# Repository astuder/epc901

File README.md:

# Introduction
The [ESPROS epc901](https://www.espros.com/photonics/epc901/) is a CCD line sensor with a resolution of 1024 monochrome pixels.

Compared to other image sensors the epc901 is very easy to drive, requiring only one voltage, I2C, a few digital I/Os and an ADC. It is also available for [$33 in single units from Digi-key](https://www.digikey.com/en/products/detail/espros-photonics-ag/EPC901-CSP32-033/10516882). On the downside, the sensor
comes in a BGA package, the evaluation kit is [very expensive at $1400](https://www.digikey.com/en/products/detail/espros-photonics-ag/EPC901-EVALUATION-KIT-V1/10516848),
and we haven't seen this sensor from any other distributors than Digi-key.

This repository contains design files to build hardware and software to interact with the sensor. 

For Windows users, there's now also a [version of g3gg0.de SpectrumPlotter](https://github.com/astuder/epc901SpectrumPlotter) adapted to work with my epc901 firmware.

@fmilburn3 posted a write-up of this project and a few spectroscopy experiments on [element14](https://www.element14.com/community/community/project14/sensors/blog/2020/11/11/spectrography-using-the-epc901-high-speed-line-image-sensor).

## Table of contents

[Hardware](#hardware)
* [Breakout board](#breakout-board)
  * [Connector pinout](#connector-pinout)
  * [Jumpers](#jumpers)
  * [Config resistor array](#config-resistor-array)
  * [Physical dimensions](#physical-dimensions)
  * [Lens holder & lens](#lens-holder--lens)
* [Adapter board](#adapter-board)
  * [Pin mapping](#pin-mapping)
  * [Jumpers](#jumpers)
* [Shared](#shared)
* [Spectroscope tube](#spectroscope-tube)

[Software](#software)
* [Firmware](#firmware)
  * [Shell](#shell)
  * [Capture logic](#capture-logic)
  * [Trigger logic](#trigger-logic)
  * [Transfer format](#transfer-format)
* [Python](#python)
  * [epc901camera.py](#epc901camerapy)
  * [example scripts](#example-scripts)
 
[License](#license)

# Hardware

All hardware in this project is designed with KiCad version 5.1.6.

The hardware consists of a breakout board for the image sensor, and an adapter board for vertically mounting the breakout board on an ST Nulceo-144 development board.

## Breakout board

The folder [```./hardware/breakout```](./hardware/breakout) contains the KiCad project for the epc901 breakout board.

The image sensor comes in a 2x16, 0.5 mm pitch BGA package and looks very fragile. With careful handling and placement, we successfully assembled a few boards
using a stainless steel solder stencil and an unmodified toaster oven for reflow. Reflow on a hotplate probably works as well.

In addition to the image sensor and related passives, the breakout board also integrates an ADC. Footprint and firmware are compatible with [Texas Instruments ADCS7476](https://www.ti.com/product/ADCS7476) and [Analog Devices AD7476](https://www.analog.com/en/products/ad7476.html) which are 1 MSPS 12-bit ADCs with SPI-like interface.

The PCB can be ordered from OSH Park using this [link](https://oshpark.com/shared_projects/5eUl3QVW).

### Connector pinout

Pin|Function|Comment
-|-|-
1|GND|digital ground
2|PWR_DOWN|see epc901 datasheet
3|DATA_RDY|see epc901 datasheet
4|CLR_DATA|see epc901 datasheet
5|SHUTTER|see epc901 datasheet
6|CLR_PIX|see epc901 datasheet
7|GNDA|analog ground
8|VIDEO_P|positive video signal for use w/ external ADC, see epc901 datasheet
9|VIDEO_N|negative video signal for use w/ external ADC, see epc901 datasheet
10|GNDA|analog ground
11|GND|digital ground
12|ADC_CLK|SPI clk to on-board ADC
13|ADC_DATA|SPI data from on-board ADC
14|ADC_CS|SPI chip select for on-board ADC
15|GND|digital ground
16|3V3|3.3V power supply
17|GND|digital ground
18|READ|see epc901 datasheet
19|SDA|I2C data
20|SCL|I2C clock

### Jumpers

ID|Function|Comment
-|-|-
JP1|STAR GND|Star ground point between GND and GNDA. Close to connect, leave open if GNDA and GND are connected off-board.
JP2|ADC SELECTION|Selects whether to use the on-board ADC or an external ADC. External ADC will route VIDEO_P to pin 8 in the connector.

### Config resistor array

These resistors control the configuration of the image sensor on power-up. For details, see sections 4, 7.1 and 12 in the epc901 datasheet.

### Physical dimensions

The size of the board is 61 x 36 mm. The mounting holes in the corners are spaced 55 x 30 mm and have a diameter of 2.2 mm, designed for M2 screws.

The mounting holes for the lens holder are located 29 mm from the left board edge and 8 mm from top and bottom board edge. They have a diameter of 2.2 mm, designed for M2 screws.

### Lens holder & lens

The breakout board has space and mounting holes for a lens holder. The spacing between the mounting holes is 20mm. For full coverage, the lens should support 1/2.3" or larger sensors.

For our prototypes, we chose a [M12 metal lens holder w/ 20mm hole spacing](https://www.m12lenses.com/CNC-Machined-M12-Lens-Holder-Metal-p/pt-lh031m.htm) and a [25mm M12 lens for 1/2" sensors](https://www.m12lenses.com/25mm-F2-4-5MP-CCTV-Lens-p/pt-2524mp5y.htm). In the US, a wide selection of lens holders and lenses can be found at [M12 Lenses Inc](https://www.m12lenses.com).

For use in a spectrograph, a lens may not be required. However we recommend protecting the sensor against accidental physical damage with some sort of bracket or baffel.

## Adapter board

The folder [```./hardware/adapter-shield```](./hardware/adapter-shield) contains the KiCad project for an adapter to mount the 
epc901 breakout board on the NUCLEO evaluation board.

The layout of the adapter board follows the Arduino Shield standard. This means you could mount the adapter and sensor breakout board on any compatible MCU board. Though
you will likely have to adapt the firmware to make it work.

The PCB can be ordered from OSH Park using this [link](https://oshpark.com/shared_projects/md99YXCX).

### Pin mapping

|Arduino|Nucleo|L496ZG|Breakout|Comment
|-|-|-|-|-
|+3V3|CN8 7|+3V3||Connected to JP1.
|+5V|CN8 9|+5V||Connected to 3.3V LDO.
|GND|CN8 11|GND|GND|
|GND|CN8 13|GND|GND|
|D0|CN10 16|PD9|PWR_DOWN|
|D1|CN10 14|PD8|DATA_RDY|
|D2|CN10 12|PF15|CLR_DATA|
|D3|CN10 10|PE13|SHUTTER|Controlled by TIM1_CH3.
|D4|CN10 8|PF14|CLR_PIX|
|D9|CN7 18|PD15|READ|
|D10|CN7 16|PD14|ADC_CS|
|D12/MISO|CN7 12|PA6|ADC_DATA|
|D13/SCK|CN7 10|PA5|ADC_CLK|
|GND|CN7 8|GND|GND|
|A0|CN9 1|PA3|VIDEO_P|
|A1|CN9 3|PC0|VIDEO_N|
||CN10 1|AVDD||Connected to JP3, reserved to supply analog power from Nucleo in future revisions.
||CN10 3|AVSS||Connected to JP4, alternative source for analog ground from Nucleo.
||CN10 5|GND|GND|
||CN10 7|PB1|VIDEO_P|Alternative analog pins for use with AVDD and AVSS connection in future revisions.
||CN10 9|PC2|VIDEO_N|Alternative analog pins for use with AVDD and AVSS connection in future revisions.

### Jumpers

ID|Function|Comment
-|-|-
JP1|3.3V VCC|Select between LDO on adapter or Nucleo (HOST) as source for 3.3V power supply to breakout board.
JP2|* GND|Star ground point between GND and GNDA. Close to connect, leave open if GNDA and GND are connected on breakout board.
JP3|AVDD|Reserved for future use to supply power to VDD_OA of the EPC901 from the Nucleo.
JP4|AVSS|Star ground point between analog ground of the breakout board and analog ground of the Nucleo. May be useful when using the ADCs of the STM32.

## Shared

The folder [```./hardware/shared```](./hardware/shared) contains custom KiCad symbols, footprints and 3d models that can be reused across KiCad projects in this repository.

## Spectroscope tube

For spectroscopy experiments we created a tube to mount an optical slit and difraction grating. The 3D model is available in the folder [```./hardware/spectroscope-tube```](./hardware/spectroscope-tube).

# Software

## Firmware

The folder [```./software/breakout```](./software/breakout) contains the firmware to control the epc901 breakout board with an
STM32L4 using the [NUCLEO-L496ZG evaluation board](https://www.digikey.com/en/products/detail/stmicroelectronics/NUCLEO-L496ZG/6697037). This specific MCU and
evaluation board were chosen because we had one laying around.

The firmware is developed and built with the latest version of STM32CubeIDE (version 1.4.2 as of October 2020). To import the project into STM32CubeIDE, clone this
repository, open STM32CubeIDE and import the project with ```File > Open Project From File System..```, and select the folder ```./software/breakout```. Follow the standard
procedure for building the firmware and programming the NUCLEO evaluation board.

### Shell

The firmware exposes a command shell over serial. The parameters of the serial connection are 115200 8N1.

Preceding a command with @ will suppress local echo and command prompt, which is useful when developing an application that interacts with the shell.

Most commands that configure an aspect of the firmware return the current setting if no value is provided. For example ```exposure``` will return the currently configured exposure time.

|Command|Description|
|-|-|
|help|Display list of available commands.|
|help COMMAND|Display help text for command.|
|echo ON/OFF|Turn local echo on or off.|
|regread REGISTER|Read register of image sensor over I2C.|
|regwrite REGISTER VALUE|Write to value to register of image sensor over I2C.|
|reset mcu|Reset the STM32 microcontroller.|
|reset camera|Reset the camera settings, for example exposure or burst, to their defaults.|
|reset sensor|Software reset of the image sensor through I2C.|
|exposure TIME_US|Set exposure time in microseconds.|
|exposure max|Get maximum exposure time supported.|
|capture|Start capture using the configured settings.|
|capture abort|If there's a capture in progress, abort current capture.|
|transfer|read next image from the frame buffer.|
|transfer all|read all images available in the frame buffer.|
|transfer last|read last image from frame buffer, all other images will be discarded.|
|burst ON/OFF|turn burst mode on or off.|
|burst fast|Turn on burst mode with fast capture, where image capture and data read out overlap. This can result in noisier data than regular burst mode.|
|burst frames COUNT|Set number of frames to capture in a burst.|
|burst interval TIME_MS|Set interval in milliseconds at which frames are captured. 0 will capture frames at the maximum speed possible.|
|trigger ON/OFF|Enable or disable trigger.|
|trigger source EXTERNAL/LEVEL/ZONE|Select source of trigger signal.|
|trigger direction RISING/FALLING|Set which direction of a signal will trigger. for ```level``` and ```zone``` rising means above/inside level/zone, falling means NOT above/inside.|
|trigger level LEVEL|Set trigger level for ```level``` trigger source.|
|trigger zone X1 Y1 X2 Y2|Set trigger zone defined by two corners for ```zone``` trigger source.|

### Capture logic

The ```capture``` command will start the image capture process based on the configuration of the camera.

First the firmware checks if there's enough space in the frame buffer for the configured number of frames (1 or burst frames). An error will be returned if there is not enoug space.

Next, if ```trigger``` is enabled, the camera waits until the configured trigger condition is met. 

Next, image capture starts. If ```burst``` is enabled, it will capture the configured number of frames. All frames captured are stored in a frame buffer. 

After the capture process is complete, images can be read from the frame buffer with the ```transfer``` command.

The shell will respond with ```BUSY``` if the camera is waiting for a trigger or a single image capture or burst is in progress. At any time, the command ```capture abort``` will return the camera back to idle state.

### Trigger logic

**External**

The external trigger source is wired to pin D35/PB11 and the USER button (B1).

Trigger direction ```rising``` triggers when the signal changes from low to high, or when the button is pressed down.
Trigger direction ```falling``` triggers when the signal changes from high to low, or when the button is released.

**Level**

The level trigger source uses live sensor data to trigger. When starting capture, the firmware will continously capture images until the trigger condition is met or capture is aborted.

Trigger direction ```rising``` triggers when a pixel is on or above the configured trigger level.
Trigger direction ```falling``` triggers when no pixel is on or above the configured trigger level.

**Zone**

The zone trigger source uses live sensor data to trigger. When starting capture, the firmware will continously capture images until the trigger condition is met or capture is aborted.

Trigger direction ```rising``` triggers when a pixel is inside the configured trigger zone.
Trigger direction ```falling``` triggers when no pixel is inside the configured trigger zone.

### Transfer format

The ```transfer``` command reads images from the frame buffer and sends them over serial. Each image is sent in two chuncks, each terminated with a linefeed. 

1. Frame metadata seperated with commas: frame number, time in milliseconds since first frame, exposure time in microseconds, number of pixels in frame
2. Frame data: a continous string with one 3-character hexadecimal number per pixel representing the brightness value

## Python

The folder [```./software/python```](./software/python) contains a Python library that wraps the shell of the
firmware, and a few useful Python scripts that use the library.

### epc901camera.py

The Python library ```epc901camera.py``` wraps the shell exposed by the firmware into an API that's easy to use from Python. 

```
from epc901camera import Camera
camera = Camera()
camera.open("my serial port")
camera.setExposure(1000)
camera.capture()
pixels = camera.getPixels()
camera.close()
```

You can use ```sendCommand()``` to directly interact with the shell, which can be useful for operations that are not supported by the library yet. The following snippet writes to I2C registers of the sensor to increase the gain.
```
camera.sendCommand("regwrite 2 0x99")  # turn on config via regs
camera.sendCommand("regwrite 0 0x19")  # 4x gain, read-out direction same as set by resistor
```

See [example scripts](#example-scripts) for more details.

### example scripts

There are three scripts to interact with the breakout board:
* ```live.py``` displays output of the image sensor in realtime
* ```snap.py``` captures one image
* ```burst.py``` captures a series of images in a burst

The scripts are controlled with shared and a few unique command line arguments.
|Argument|```live.py```|```snap.py```|```burst.py```|Description|
|-|-|-|-|-|
|-h, --help|:heavy_check_mark:|:heavy_check_mark:|:heavy_check_mark:|Display help text.|
|-p PORT|:heavy_check_mark:|:heavy_check_mark:|:heavy_check_mark:|Serial port which connects to the camera board, this is the only required argument.|
|-e EXPOSURE|:heavy_check_mark:|:heavy_check_mark:|:heavy_check_mark:|Set exposure time in microseconds. If not specified, the default exposure time is 1ms (1000us).|
|-t {external,level,zone}||:heavy_check_mark:|:heavy_check_mark:|Enable trigger and select trigger source. See [Trigger logic](#trigger-logic).|
|-tdir {falling,rising}||:heavy_check_mark:|:heavy_check_mark:|Set direction of trigger logic.|
|-tl TRIG_LEVEL||:heavy_check_mark:|:heavy_check_mark:|Set brightness for level trigger. Valid values are 0-4095.|
|-tz x1,y1,x2,y2||:heavy_check_mark:|:heavy_check_mark:|Define rectangle for zone trigger. Valid x values are 0-1023, valid y values are 0-4095.|
|-td TRIG_DELAY||:heavy_check_mark:|:heavy_check_mark:|Set delay in milliseconds after trigger event before image capture starts.|
|-f FRAMES|||:heavy_check_mark:|Number of frames to capture in a burst.|
|-i INTERVAL|||:heavy_check_mark:|Set time interval in milliseconds between frames. 0 means best effort, i.e. at maximum speed possible. As it takes 1.3ms to read out a frame, effective capture rates may be lower than the configured interval. |
|-fast|||:heavy_check_mark:|Enable special burst mode where frames are read out of the sensor while the next exposure is captured. This may increase noise, but will increase effective burst speeds.|
|-gq||:heavy_check_mark:|:heavy_check_mark:|Don't display graph window.|
|-g GRAPH_TYPE|||:heavy_check_mark:|Display animated 2D graph or 3D surface plot. If argument is missing, no graph will be displayed.|
|-gc COLOR|||:heavy_check_mark:|Select alternative color map for 3D graph.|
|-gpng GRAPH_FILE||:heavy_check_mark:|:heavy_check_mark:|Save graph as PNG file.|
|-png PNG_FILE||:heavy_check_mark:|:heavy_check_mark:|Save sensor data as a gray-scale bitmap in a PNG file.|
|-csv CSV_FILE||:heavy_check_mark:|:heavy_check_mark:|Save sensor data as CSV file.|
|-a|:heavy_check_mark:|:heavy_check_mark:|:heavy_check_mark:|Automatically scale vertical axis of graphs based on image data. If not specified, the Y axis will go from 0 to 3000.|
|-sx px1,w1,px2,w2|:heavy_check_mark:|:heavy_check_mark:|:heavy_check_mark:|Scale labels of horizontal axis of 2D graphs by linear interpolation based on two points, for example to reflect wavelengths in a spectrograph. If not specified, the X axis will be labelled with pixel positions 0-1024.|

# License

Unless stated otherwise, all software in this project is licensed under the terms of MIT License.

The main exception are files imported from the STM32 SDK ([```./software/breakout/Drivers```](./software/breakout/Drivers)), and a few files
auto-generated by STM32CubeIDE. See source code for applicable license terms.

All hardware in this project is licensed under the terms of CERN Open Hardware Licence Version 2 - Permissive.

See [LICENSE-SW](LICENSE-SW) and [LICENSE-HW](LICENSE-HW) for additional details.

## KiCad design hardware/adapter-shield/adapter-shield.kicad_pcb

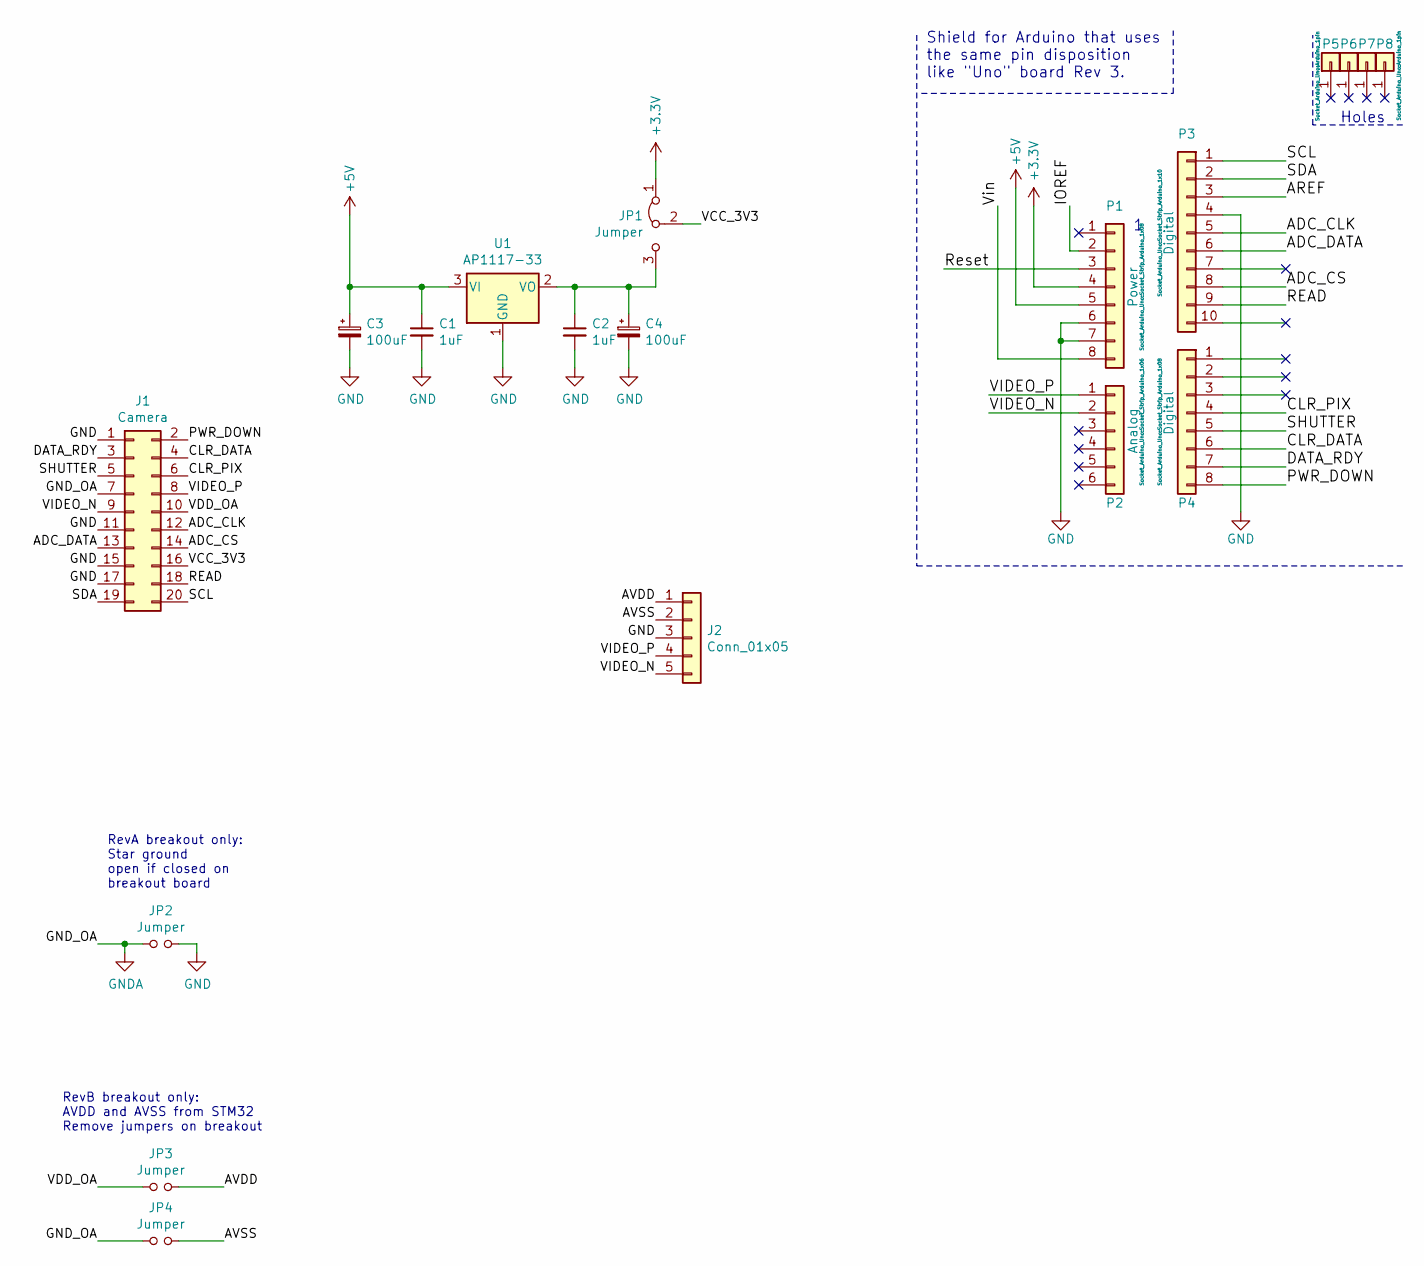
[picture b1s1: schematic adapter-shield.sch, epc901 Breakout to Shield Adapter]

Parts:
C1, C2: 1uF; C_0805_2012Metric
C3, C4: 100uF; CP_Radial_D5.0mm_P2.50mm
J1: Camera; PinSocket_2x10_P2.54mm_Vertical
J2: Conn_01x05; PinHeader_1x05_P2.54mm_Vertical
JP1: Jumper; PinHeader_1x03_P2.54mm_Vertical
JP2, JP3, JP4: Jumper; PinHeader_1x02_P2.54mm_Vertical
P1: Power; Socket_Strip_Arduino_1x08
P2: Analog; Socket_Strip_Arduino_1x06
P3: Digital; Socket_Strip_Arduino_1x10
P4: Digital; Socket_Strip_Arduino_1x08
P5, P6, P7, P8: CONN_01X01; Arduino_1pin
U1: AP1117-33; SOT-223-3_TabPin2

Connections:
+3V3: JP1.1 (A), P1.4
+5V: C1.1, C3.1, P1.5, U1.3 (VI)
/ADC_CLK: J1.12, P3.5
/ADC_CS: J1.14, P3.8
/ADC_DATA: J1.13, P3.6
/AREF: P3.3
/AVDD: J2.1, JP3.2
/AVSS: J2.2, JP4.2
/CLR_DATA: J1.4, P4.6
/CLR_PIX: J1.6, P4.4
/DATA_RDY: J1.3, P4.7
/IOREF: P1.2
/PWR_DOWN: J1.2, P4.8
/READ: J1.18, P3.9
/Reset: P1.3
/SCL: J1.20, P3.1
/SDA: J1.19, P3.2
/SHUTTER: J1.5, P4.5
/VCC_3V3: J1.16, JP1.2 (C)
/VDD_OA: J1.10, JP3.1
/VIDEO_N: J1.9, J2.5, P2.2
/VIDEO_P: J1.8, J2.4, P2.1
/Vin: P1.8
GND: C1.2, C2.2, C3.2, C4.2, J1.1, J1.11, J1.15, J1.17, J2.3, JP2.2, P1.6, P1.7, P3.4, U1.1 (GND)
GNDA: J1.7, JP2.1, JP4.1
unnamed: C2.1, C4.1, JP1.3 (B), U1.2 (VO)

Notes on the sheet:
Holes
Shield for Arduino that uses the same pin disposition like "Uno" board Rev 3.
RevA breakout only: Star ground open if closed on breakout board
RevB breakout only: AVDD and AVSS from STM32 Remove jumpers on breakout

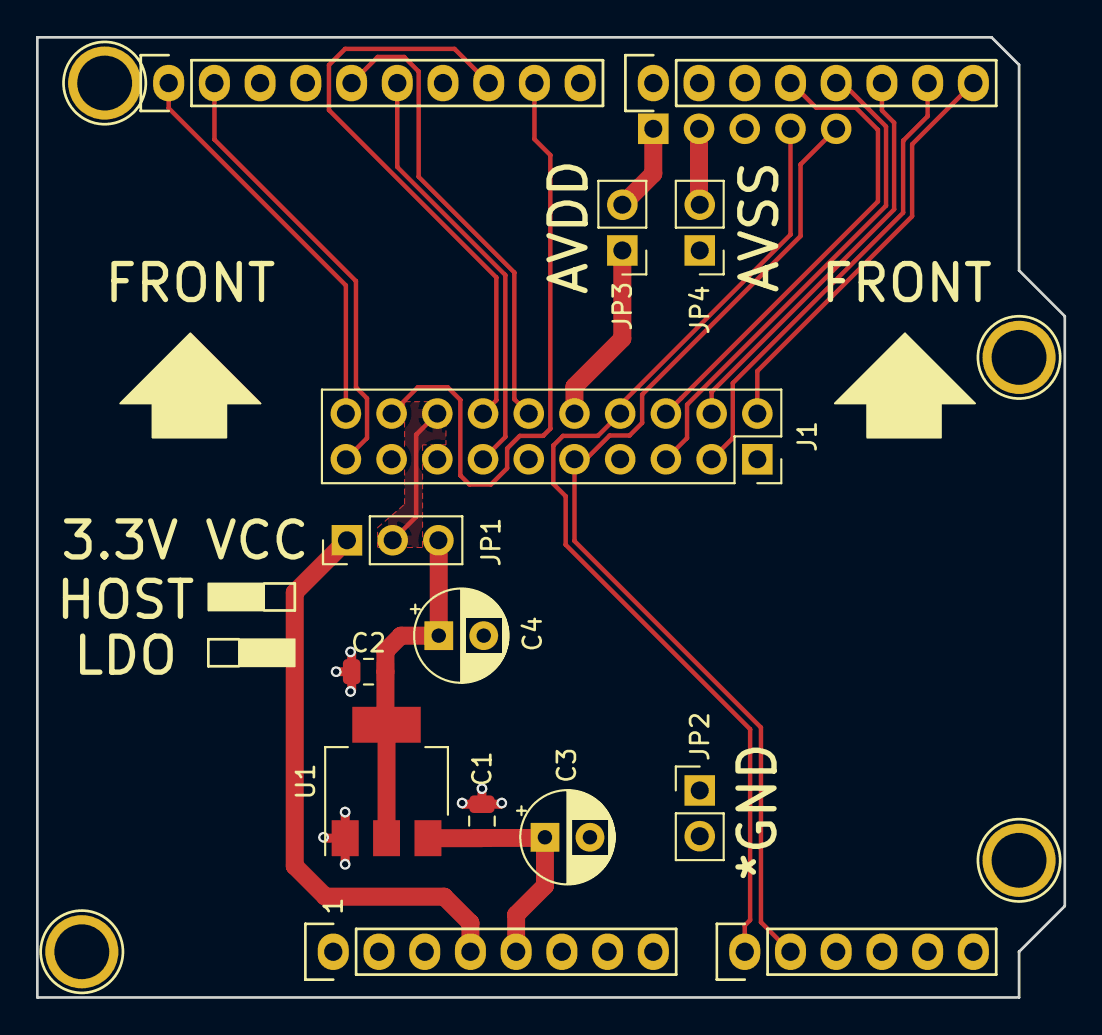
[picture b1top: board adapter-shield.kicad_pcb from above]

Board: 2 copper layers, 57.1 x 53.3 mm, 19 parts (1 on the bottom side), 22 nets.

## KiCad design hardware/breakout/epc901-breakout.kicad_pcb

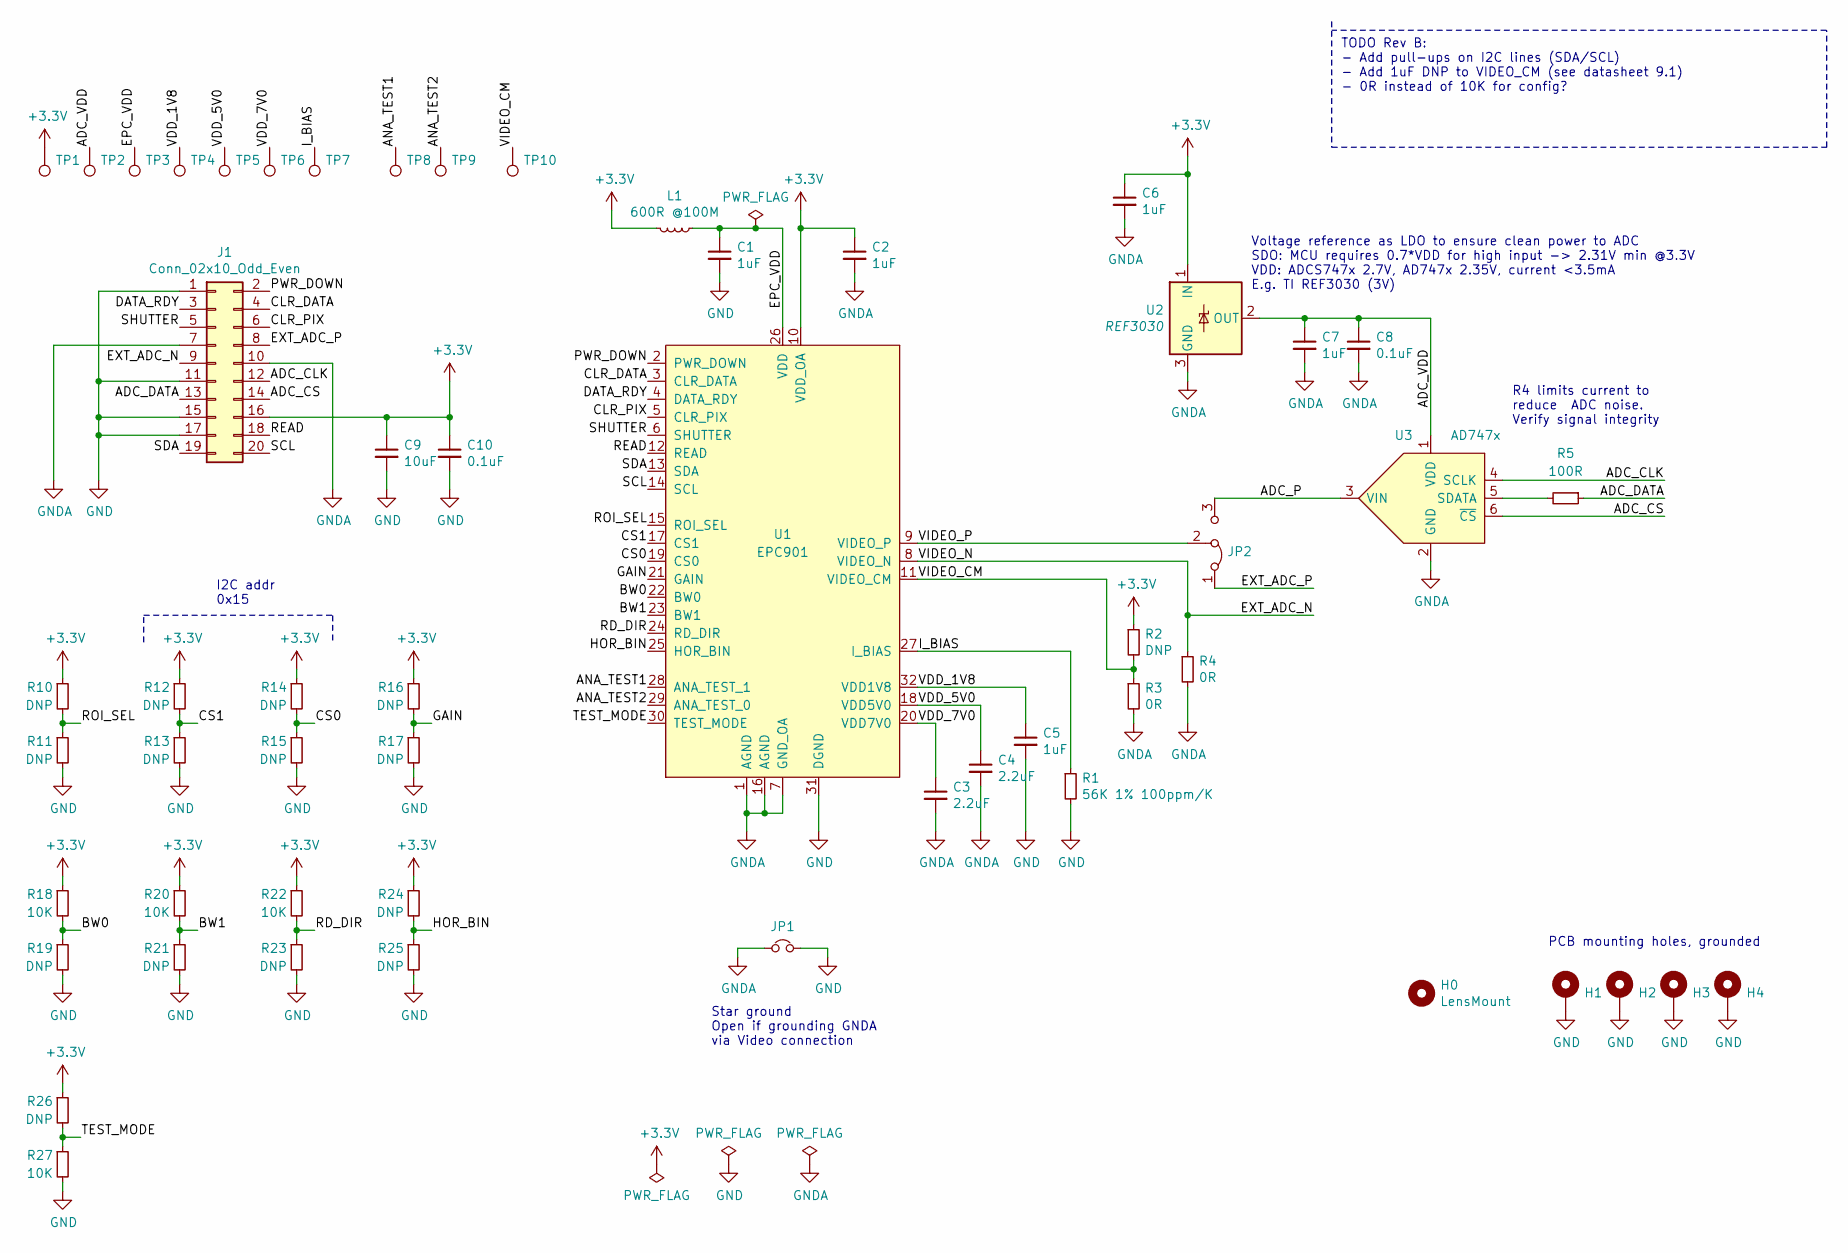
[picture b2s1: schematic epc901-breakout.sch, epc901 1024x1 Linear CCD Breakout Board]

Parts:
C1, C2, C5, C6, C7: 1uF; C_0603_1608Metric
C3, C4: 2.2uF; C_0603_1608Metric
C8, C10: 0.1uF; C_0603_1608Metric
C9: 10uF; C_0805_2012Metric
H0: LensMount; lensholder-m12-20mm
H1, H2, H3, H4: MountingHole_Pad; MountingHole_2.2mm_M2_DIN965_Pad
J1: Conn_02x10_Odd_Even; PinHeader_2x10_P2.54mm_Vertical
JP1: Jumper_NC_Small; PinHeader_1x02_P2.54mm_Vertical
JP2: Jumper_3_Bridged12; PinHeader_1x03_P2.54mm_Vertical
L1: 600R @100M; L_0603_1608Metric; Mpn BLM18TG601TN1D
R1: 56K 1% 100ppm/K; R_0603_1608Metric
R2, R10, R11, R12, R13, R14, R15, R16, R17, R19, R21, R23, R24, R25, R26: DNP; R_0603_1608Metric
R3, R4: 0R; R_0603_1608Metric
R5: 100R; R_0603_1608Metric
R18, R20, R22, R27: 10K; R_0603_1608Metric
TP1, TP2, TP3, TP4, TP5, TP6, TP7, TP8, TP9, TP10: TestPoint; TestPoint_Pad_D1.0mm
U1: EPC901; epc901; Mpn EPC901-CSP32-033
U2: REF3030; SOT-23; Mpn REF3030AIDBZR
U3: AD747x; SOT-23-6; Mpn ADCS7476AIMF/NOPB‎

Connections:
+3V3: C2.1, C6.1, C9.1, C10.1, J1.16, L1.2, R2.1, R10.1, R12.1, R14.1, R16.1, R18.1, R20.1, R22.1, R24.1, R26.1, TP1.1, U1.10 (VDD_OA), U2.1 (IN)
/ADC_CLK: J1.12, U3.4 (SCLK)
/ADC_CS: J1.14, U3.6 (~CS)
/ADC_DATA: J1.13, R5.1
/ADC_P: JP2.3 (B), U3.3 (VIN)
/ADC_VDD: C7.1, C8.1, TP2.1, U2.2 (OUT), U3.1 (VDD)
/ANA_TEST1: TP8.1, U1.28 (ANA_TEST_1)
/ANA_TEST2: TP9.1, U1.29 (ANA_TEST_0)
/BW0: R18.2, R19.1, U1.22 (BW0)
/BW1: R20.2, R21.1, U1.23 (BW1)
/CLR_DATA: J1.4, U1.3 (CLR_DATA)
/CLR_PIX: J1.6, U1.5 (CLR_PIX)
/CS0: R14.2, R15.1, U1.19 (CS0)
/CS1: R12.2, R13.1, U1.17 (CS1)
/DATA_RDY: J1.3, U1.4 (DATA_RDY)
/EPC_VDD: C1.1, L1.1, TP3.1, U1.26 (VDD)
/EXT_ADC_N: J1.9, R4.1, U1.8 (VIDEO_N)
/EXT_ADC_P: J1.8, JP2.1 (A)
/GAIN: R16.2, R17.1, U1.21 (GAIN)
/HOR_BIN: R24.2, R25.1, U1.25 (HOR_BIN)
/I_BIAS: R1.1, TP7.1, U1.27 (I_BIAS)
/PWR_DOWN: J1.2, U1.2 (PWR_DOWN)
/RD_DIR: R22.2, R23.1, U1.24 (RD_DIR)
/READ: J1.18, U1.12 (READ)
/ROI_SEL: R10.2, R11.1, U1.15 (ROI_SEL)
/SCL: J1.20, U1.14 (SCL)
/SDA: J1.19, U1.13 (SDA)
/SHUTTER: J1.5, U1.6 (SHUTTER)
/TEST_MODE: R26.2, R27.1, U1.30 (TEST_MODE)
/VDD_1V8: C5.1, TP4.1, U1.32 (VDD1V8)
/VDD_5V0: C4.1, TP5.1, U1.18 (VDD5V0)
/VDD_7V0: C3.1, TP6.1, U1.20 (VDD7V0)
/VIDEO_CM: R2.2, R3.1, TP10.1, U1.11 (VIDEO_CM)
/VIDEO_P: JP2.2 (C), U1.9 (VIDEO_P)
GND: C1.2, C5.2, C9.2, C10.2, H1.1, H2.1, H3.1, H4.1, J1.1, J1.11, J1.15, J1.17, JP1.2, R1.2, R11.2, R13.2, R15.2, R17.2, R19.2, R21.2, R23.2, R25.2, R27.2, U1.31 (DGND)
GNDA: C2.2, C3.2, C4.2, C6.2, C7.2, C8.2, J1.7, J1.10, JP1.1, R3.2, R4.2, U1.1 (AGND), U1.7 (GND_OA), U1.16 (AGND), U2.3 (GND), U3.2 (GND)
unnamed: R5.2, U3.5 (SDATA)

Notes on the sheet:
Voltage reference as LDO to ensure clean power to ADC SDO: MCU requires 0.7*VDD for high input -> 2.31V min @3.3V VDD: ADCS747x 2.7V, AD747x 2.35V, current <3.5mA E.g. TI REF3030 (3V)
I2C addr 0x15
PCB mounting holes, grounded
R4 limits current to reduce ADC noise. Verify signal integrity
Star ground Open if grounding GNDA via Video connection
TODO Rev B: - Add pull-ups on I2C lines (SDA/SCL) - Add 1uF DNP to VIDEO_CM (see datasheet 9.1) - 0R instead of 10K for config?

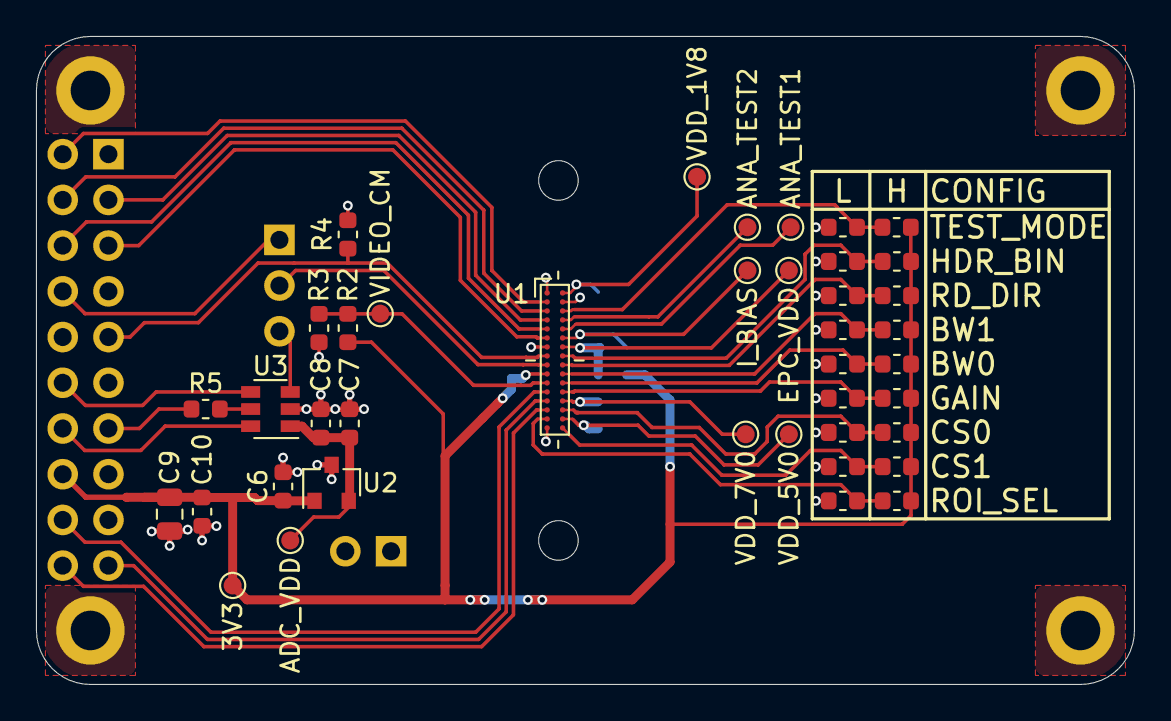
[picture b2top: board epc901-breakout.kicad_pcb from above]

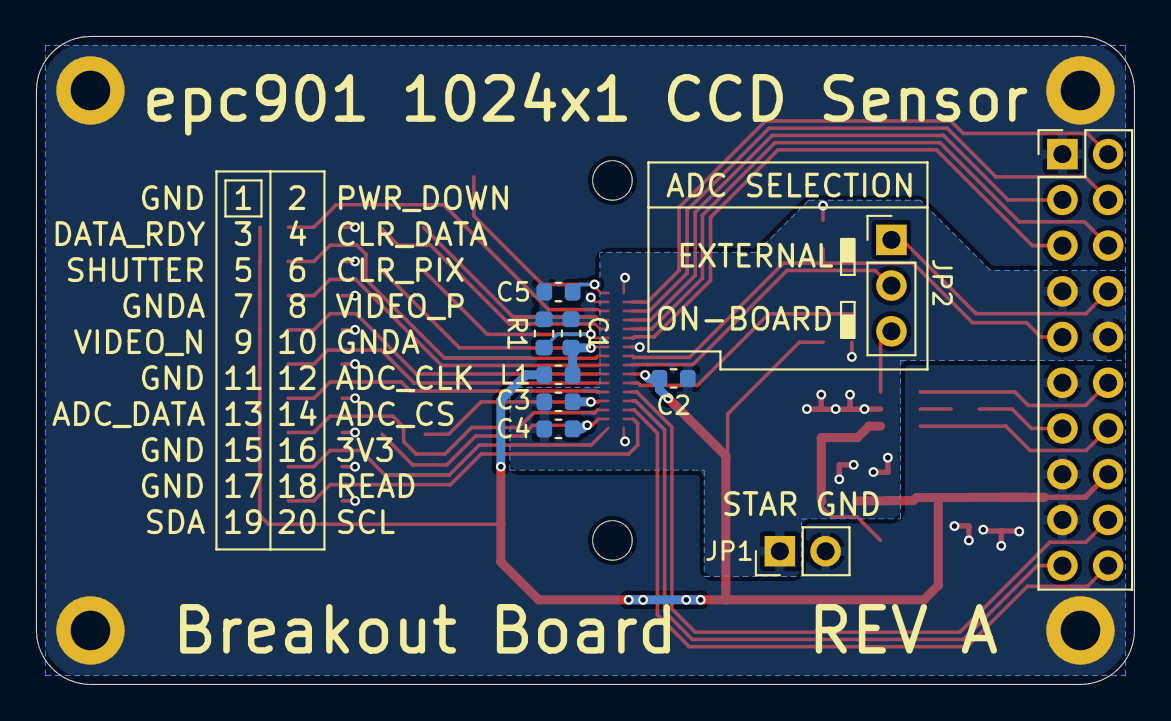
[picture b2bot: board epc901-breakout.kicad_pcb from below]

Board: 2 copper layers, 61.0 x 36.0 mm, 55 parts (10 on the bottom side), 37 nets.

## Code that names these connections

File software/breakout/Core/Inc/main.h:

/* USER CODE BEGIN Header */
/**
  ******************************************************************************
  * @file           : main.h
  * @brief          : Header for main.c file.
  *                   This file contains the common defines of the application.
  ******************************************************************************
  * @attention
  *
  * <h2><center>&copy; Copyright (c) 2020 STMicroelectronics.
  * All rights reserved.</center></h2>
  *
  * This software component is licensed by ST under BSD 3-Clause license,
  * the "License"; You may not use this file except in compliance with the
  * License. You may obtain a copy of the License at:
  *                        opensource.org/licenses/BSD-3-Clause
  *
  ******************************************************************************
  */
/* USER CODE END Header */

/* Define to prevent recursive inclusion -------------------------------------*/
#ifndef __MAIN_H
#define __MAIN_H

#ifdef __cplusplus
extern "C" {
#endif

/* Includes ------------------------------------------------------------------*/
#include "stm32l4xx_hal.h"

/* Private includes ----------------------------------------------------------*/
/* USER CODE BEGIN Includes */
/* USER CODE END Includes */

/* Exported types ------------------------------------------------------------*/
/* USER CODE BEGIN ET */

/* USER CODE END ET */

/* Exported constants --------------------------------------------------------*/
/* USER CODE BEGIN EC */

/* USER CODE END EC */

/* Exported macro ------------------------------------------------------------*/
/* USER CODE BEGIN EM */

/* USER CODE END EM */

void HAL_TIM_MspPostInit(TIM_HandleTypeDef *htim);

/* Exported functions prototypes ---------------------------------------------*/
void Error_Handler(void);

/* USER CODE BEGIN EFP */

/* USER CODE END EFP */

/* Private defines -----------------------------------------------------------*/
#define B1_Pin GPIO_PIN_13
#define B1_GPIO_Port GPIOC
#define B1_EXTI_IRQn EXTI15_10_IRQn
#define ADC_CLK_Pin GPIO_PIN_5
#define ADC_CLK_GPIO_Port GPIOA
#define ADC_DATA_Pin GPIO_PIN_6
#define ADC_DATA_GPIO_Port GPIOA
#define CLR_PIX_Pin GPIO_PIN_14
#define CLR_PIX_GPIO_Port GPIOF
#define CLR_DATA_Pin GPIO_PIN_15
#define CLR_DATA_GPIO_Port GPIOF
#define SHUTTER_Pin GPIO_PIN_13
#define SHUTTER_GPIO_Port GPIOE
#define TRIGGER_Pin GPIO_PIN_11
#define TRIGGER_GPIO_Port GPIOB
#define TRIGGER_EXTI_IRQn EXTI15_10_IRQn
#define LD3_Pin GPIO_PIN_14
#define LD3_GPIO_Port GPIOB
#define DATA_RDY_Pin GPIO_PIN_8
#define DATA_RDY_GPIO_Port GPIOD
#define PWR_DOWN_Pin GPIO_PIN_9
#define PWR_DOWN_GPIO_Port GPIOD
#define ADC_CS_Pin GPIO_PIN_14
#define ADC_CS_GPIO_Port GPIOD
#define READ_Pin GPIO_PIN_15
#define READ_GPIO_Port GPIOD
#define USB_OverCurrent_Pin GPIO_PIN_5
#define USB_OverCurrent_GPIO_Port GPIOG
#define USB_PowerSwitchOn_Pin GPIO_PIN_6
#define USB_PowerSwitchOn_GPIO_Port GPIOG
#define STLK_RX_Pin GPIO_PIN_7
#define STLK_RX_GPIO_Port GPIOG
#define STLK_TX_Pin GPIO_PIN_8
#define STLK_TX_GPIO_Port GPIOG
#define LD1_Pin GPIO_PIN_7
#define LD1_GPIO_Port GPIOC
#define USB_SOF_Pin GPIO_PIN_8
#define USB_SOF_GPIO_Port GPIOA
#define USB_VBUS_Pin GPIO_PIN_9
#define USB_VBUS_GPIO_Port GPIOA
#define USB_ID_Pin GPIO_PIN_10
#define USB_ID_GPIO_Port GPIOA
#define USB_DM_Pin GPIO_PIN_11
#define USB_DM_GPIO_Port GPIOA
#define USB_DP_Pin GPIO_PIN_12
#define USB_DP_GPIO_Port GPIOA
#define TMS_Pin GPIO_PIN_13
#define TMS_GPIO_Port GPIOA
#define TCK_Pin GPIO_PIN_14
#define TCK_GPIO_Port GPIOA
#define SWO_Pin GPIO_PIN_3
#define SWO_GPIO_Port GPIOB
#define LD2_Pin GPIO_PIN_7
#define LD2_GPIO_Port GPIOB
#define I2C_SCL_Pin GPIO_PIN_8
#define I2C_SCL_GPIO_Port GPIOB
#define I2C_SDA_Pin GPIO_PIN_9
#define I2C_SDA_GPIO_Port GPIOB
/* USER CODE BEGIN Private defines */

/* USER CODE END Private defines */

#ifdef __cplusplus
}
#endif

#endif /* __MAIN_H */

/************************ (C) COPYRIGHT STMicroelectronics *****END OF FILE****/

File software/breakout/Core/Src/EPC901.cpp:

/*
 * Integration with epc901 sensor.
 *
 * Copyright 2020 by Adrian Studer
 *
 * Licensed under the terms of MIT License, all text here must be included in any redistribution.
 * See the LICENSE-SW file for details.
 */

#include "main.h"
#include "EPC901.hpp"
#include "dwt_stm32_delay.h"
#include <inttypes.h>
#include <cstring>

const uint8_t EPC_I2C_ADDR = 0x15;

EPC901::EPC901() {
	_chip_rev = 0;
	_i2c_addr = EPC_I2C_ADDR << 1;
	_i2c_handle = 0;
	_power_state = 0;
}

EPC901::~EPC901() {
}

uint8_t EPC901::init(I2C_HandleTypeDef* i2c_handle, uint8_t i2c_addr, SPI_HandleTypeDef* spi_handle, TIM_HandleTypeDef* tim_handle) {
	_i2c_handle = i2c_handle;
	if (i2c_addr != 0) {
		_i2c_addr = i2c_addr << 1;
	}
	_spi_handle = spi_handle;
	_tim_handle = tim_handle;

	// set all pins to sane defaults
	HAL_GPIO_WritePin(PWR_DOWN_GPIO_Port, PWR_DOWN_Pin, GPIO_PIN_SET);
	HAL_GPIO_WritePin(CLR_DATA_GPIO_Port, CLR_DATA_Pin, GPIO_PIN_RESET);
	HAL_GPIO_WritePin(CLR_PIX_GPIO_Port, CLR_PIX_Pin, GPIO_PIN_RESET);
	HAL_GPIO_WritePin(READ_GPIO_Port, READ_Pin, GPIO_PIN_RESET);
	HAL_GPIO_WritePin(ADC_CS_GPIO_Port, ADC_CS_Pin, GPIO_PIN_SET);

	// configure and enable SPI peripheral
	__HAL_LOCK(_spi_handle);
	SET_BIT(_spi_handle->Instance->CR2, SPI_RXFIFO_THRESHOLD);
	__HAL_SPI_ENABLE(_spi_handle);
	__HAL_UNLOCK(_spi_handle);

	// enable one pulse timer
	HAL_TIM_OnePulse_Start(_tim_handle, TIM_CHANNEL_1);
	// enable CH3 which is not full supported in HAL
	TIM_CCxChannelCmd(_tim_handle->Instance, TIM_CHANNEL_3, TIM_CCx_ENABLE);

	// init sensor
	_powerUp();

	// read chip revision

	uint8_t revision;
	if (HAL_OK == HAL_I2C_Mem_Read(_i2c_handle, _i2c_addr, 0xff, 1, &revision, 1, 100)) {
		_chip_rev = revision;
	} else {
		_powerDown();
		return 1;
	}

	// TODO: oscillator calibration
	// may be negligible for exposure times >1us

	_powerDown();

	return 0;
}

uint16_t EPC901::captureImage(uint32_t exposure_us, uint16_t* buffer) {
	if (exposure_us > _max_exposure_us) {
		return 0;
	}
	_powerUp();
	_clear();
	_exposeImage(exposure_us);
	uint16_t pixels = _readImage(buffer);
	_powerDown();
	return pixels;
}

uint8_t EPC901::getRevision() {
	return _chip_rev;
}

uint8_t EPC901::readRegister(uint8_t address, uint8_t* value) {
	uint8_t val = 0;
	uint8_t err = 0;
	_powerUp();
	err = HAL_I2C_Mem_Read(_i2c_handle, _i2c_addr, address, 1, &val, 1, 100);
	if (err == HAL_OK) {
		*value = val;
	}
	_powerDown();
	return err;
}

uint8_t EPC901::writeRegister(uint8_t address, uint8_t value) {
	uint8_t val = value;
	uint8_t err = 0;
	_powerUp();
	err = HAL_I2C_Mem_Write(_i2c_handle, _i2c_addr, address, 1, &val, 1, 100);
	_powerDown();

	// update variables that influence pixel count
	if (err == HAL_OK) {
		if (address == 0x00) {
			_roi_sel = (value >> 1) & 0x01;	// region of interest
			_hor_bin = (value >> 4) & 0x03;	// binning
		}
		if (address == 0x02) {
			_conf_ctrl = value & 0x01;	// configuration control
		}
	}

	return err;
}

uint8_t EPC901::reset(void) {
	uint8_t val = 6;
	uint8_t err = 0;
	_powerUp();
	err = HAL_I2C_Master_Transmit(_i2c_handle, 0, &val, 1, 100);
	_powerDown();

	// set binning, roi and configuration control to defaults
	// if hor_bin or roi_sel is set differently with pins, this needs to be adjusted
	_hor_bin = 1;	// no binning
	_roi_sel = 0;	// all pixels
	_conf_ctrl = 0;	// configuration controlled by pins

	return err;
}

void EPC901::_powerUp() {
	// power up sensor
	HAL_GPIO_WritePin(PWR_DOWN_GPIO_Port, PWR_DOWN_Pin, GPIO_PIN_RESET);
	DWT_Delay_us(12);
	_power_state = 1;
}

void EPC901::_powerDown() {
	// power down sensor
	HAL_GPIO_WritePin(PWR_DOWN_GPIO_Port, PWR_DOWN_Pin, GPIO_PIN_SET);
	_power_state = 0;
}

void EPC901::_clear() {
	// clear data (necessary when using power-down?)
	HAL_GPIO_WritePin(CLR_DATA_GPIO_Port, CLR_DATA_Pin, GPIO_PIN_SET);
	DWT_Delay_us(2);
	HAL_GPIO_WritePin(CLR_DATA_GPIO_Port, CLR_DATA_Pin, GPIO_PIN_RESET);
	DWT_Delay_us(20);

	// clear pixels (necessary when using power-down?)
	HAL_GPIO_WritePin(CLR_PIX_GPIO_Port, CLR_PIX_Pin, GPIO_PIN_SET);
	DWT_Delay_us(2);
	HAL_GPIO_WritePin(CLR_PIX_GPIO_Port, CLR_PIX_Pin, GPIO_PIN_RESET);
	DWT_Delay_us(20);
}

void EPC901::_exposeImage(uint32_t exposure_us) {
	if (_power_state == 0) {
		_powerUp();
		_clear();
	}

	// calculate exposure in clk ticks
	uint32_t exposure_clk = exposure_us * 80;
	// set prescaler
	if (exposure_clk >= 0xffffff) {
		exposure_clk = exposure_clk >> 16;
		__HAL_TIM_SET_PRESCALER(_tim_handle, 0xffff);
	} else if (exposure_clk >= 0xffff) {
		exposure_clk = exposure_clk >> 8;
		__HAL_TIM_SET_PRESCALER(_tim_handle, 0xff);
	} else {
		__HAL_TIM_SET_PRESCALER(_tim_handle, 0);
	}
	// set pulse_start
	_tim_handle->Instance->CCR3 = 1;
	// set pulse end
	_tim_handle->Instance->ARR = 1 + exposure_clk;
	// force timer to reload values
	_tim_handle->Instance->EGR = TIM_EGR_UG;
	// start pulse
	__HAL_TIM_ENABLE(_tim_handle);

	// timer stops automatically when done
}

// Reading pixel from sensor using ADC on breakout board:
//   set ADC CS low - sample HOLD
//   start SPI transfer of 2 bytes from ADC
//   set READ high
//   wait for and read 1 byte from SPI/ADC
//   set READ low
//   wait for and read 1 byte from SPI/ADC (ADC automatically switches to SAMPLE on 13th bit)
//   set ADC CS high
#define __readADC() ({	\
		ADC_CS_GPIO_Port->BRR = (uint32_t)ADC_CS_Pin; \
		spi->DR = (uint16_t) 0; \
		READ_GPIO_Port->BSRR = (uint32_t)READ_Pin; \
		while (!(spi->SR & SPI_FLAG_RXNE)); \
		READ_GPIO_Port->BRR = (uint32_t)READ_Pin; \
		data_msb = *(__IO uint8_t *)&spi->DR; \
		while (!(spi->SR & SPI_FLAG_RXNE)); \
		data_lsb = *(__IO uint8_t *)&spi->DR; \
		ADC_CS_GPIO_Port->BSRR = (uint32_t)ADC_CS_Pin; \
		})
// don't clock READ during last ADC conversion
#define __finishADC() ({	\
		ADC_CS_GPIO_Port->BRR = (uint32_t)ADC_CS_Pin; \
		spi->DR = (uint16_t) 0; \
		while (!(spi->SR & SPI_FLAG_RXNE)); \
		data_msb = *(__IO uint8_t *)&spi->DR; \
		while (!(spi->SR & SPI_FLAG_RXNE)); \
		data_lsb = *(__IO uint8_t *)&spi->DR; \
		ADC_CS_GPIO_Port->BSRR = (uint32_t)ADC_CS_Pin; \
		})


uint16_t EPC901::_readImage(uint16_t* buffer) {
	// wait for data ready
	while (GPIO_PIN_RESET == HAL_GPIO_ReadPin(DATA_RDY_GPIO_Port, DATA_RDY_Pin)) {
		// TODO: timeout?
	}

	// read pulse
	HAL_GPIO_WritePin(READ_GPIO_Port, READ_Pin, GPIO_PIN_SET);
	// wait 3 osc cycles - ~0.1us with osc ~36MHz
	DWT_Delay_us(1);
	HAL_GPIO_WritePin(READ_GPIO_Port, READ_Pin, GPIO_PIN_RESET);
	// wait for conversion (37-3 osc cycles) - ~1us with osc ~36MHz
	DWT_Delay_us(2);

	// lock SPI handle
	__HAL_LOCK(_spi_handle);
	SPI_TypeDef* spi = _spi_handle->Instance;

	// determine number of pixels per frame
	uint16_t pixel_cnt = 1024;
	if (_conf_ctrl) {	// configuration is controlled by registers
		if (_roi_sel) {		// only center half of pixels are captured
			pixel_cnt /= 2;
		}
		if (_hor_bin == 0) {	// binning 2 pixels
			pixel_cnt /= 2;
		} else if (_hor_bin == 2) {	// binning 4 pixels
			pixel_cnt /= 4;
		}
	}

	// read pixels
	uint16_t count;
	uint8_t data_msb, data_lsb;

	// discard first 4 samples (3 pre-loading cycles, 1 ADC sample/conversion pipeline)
	count = 4;
	do {
		__readADC();
		count--;
	} while (count != 0);

	// read pixels
	count = pixel_cnt - 1;
	do {
		__readADC();
		// store pixel
		*buffer = (data_msb << 7) | (data_lsb >> 1);
		buffer++;
		count--;
	} while (count != 0);

	// Don't wiggle READ when reading last pixel
	__finishADC();
	*buffer = (data_msb << 7) | (data_lsb >> 1);

	// release SPI peripheral
	__HAL_UNLOCK(_spi_handle);

	return pixel_cnt;
}

uint8_t EPC901::_dataReady() {
	return GPIO_PIN_SET == HAL_GPIO_ReadPin(DATA_RDY_GPIO_Port, DATA_RDY_Pin);
}

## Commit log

2020-10-08 reduce overhead of us delay from 0.7us to 0.2us
2020-10-08 minor clean-up in capture loop
2020-10-08 port and exposure as cmd line arguments
2020-10-08 split epc901 camera class into its own library
2020-10-08 add snap.py, reset sensor when opening camera
2020-10-08 add option to automatically scale image data
2020-10-08 add burst, fix bugs
2020-10-09 remove debug msg
2020-10-09 renamed burst delay to interval
2020-10-09 add timestamp to burst 3d plot
2020-10-09 improved plot, discard first frame in burst
2020-10-09 add spectrum as color option for burst
2020-10-10 Implement transfer all command
2020-10-10 Optimize SPI transfer (597->746fps)
2020-10-10 updated comment
2020-10-10 Change format of transfered image data from hex4 to hex3
2020-10-10 optimize loop for reading image (746fps -> 785fps)
2020-10-10 more even READ clock
2020-10-10 add cmd 'transfer last' to read newest frame and discard the rest
2020-10-10 don't clk READ during last ADC conversion
2020-10-11 breakout to shield adapter
2020-10-11 cleanup sheet info
2020-10-11 Control shutter with TIM1 timer peripheral
2020-10-11 enable one pulse timer only once
2020-10-13 add method to encapsulate sending commands
2020-10-13 added fast burst mode, fixed clearing of sensor
2020-10-13 increase serial timeout
2020-10-13 add option to save data to CSV file
2020-10-14 animated 2d graph for burst, some clean-up
2020-10-14 save snap csv as a single row, save correct number of frames for burst animation
2020-10-19 Refactored capture to be async, fixed UART crash
2020-10-23 add trigger functionality
2020-10-25 changed pinout to match adapter board
2020-10-25 Fixed link for ADCS
2020-10-26 document breakout board
2020-10-26 add drawing of dimensions, schematics as pdf
2020-10-26 Fixed image
2020-10-27 adding photo of hardware
2020-10-27 document adapter board
2020-10-27 Add table of contents
2020-10-28 document shell and capture logic
2020-10-28 update table of contents
2020-10-30 fixed clearing of sensor via pins
2020-10-30 fix #2
2020-11-03 Add license file for software
2020-11-03 Add license info
2020-11-03 Add copyright notices to source code
2020-11-03 Edit license information
2020-11-04 Document command line arguments of python scripts
2020-11-04 rename trigger region to zone, and fix it
2020-11-04 fix -sx for 2d plot
2020-11-04 Clarify -xs option
2020-11-04 update/fix command description
2020-11-04 edited for typos, formatting, clarity
2020-11-05 Add example for sendCommand
2020-11-05 typo
2020-11-07 support binning and region of interest on low level
2020-11-07 Document pixel count in shell command transfer
2020-11-09 Add 3D model for spectroscope tube
2020-11-11 Add link to article on element14
2020-11-11 Add license information to hardware design files
2020-11-11 Add links to shared projects on OSH Park
2020-11-30 add delays to ensure max burst speeds
2020-12-01 Fixed I2C address configuration during init
2020-12-02 use relative path for links within repository
2020-12-28 add sublime to gitignore
2021-03-25 rear view of assembled hardware
2022-03-06 link to epc901 SpectrumPlotter
2023-03-03 update prices of sensor and dev-kit

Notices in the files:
README.md:
License:
Unless stated otherwise, all software in this project is licensed under the terms of MIT License.
The main exception are files imported from the STM32 SDK ([```./software/breakout/Drivers```](./software/breakout/Drivers)), and a few files
auto-generated by STM32CubeIDE. See source code for applicable license terms.
All hardware in this project is licensed under the terms of CERN Open Hardware Licence Version 2 - Permissive.
See [LICENSE-SW](LICENSE-SW) and [LICENSE-HW](LICENSE-HW) for additional details.
